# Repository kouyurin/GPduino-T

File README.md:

GPduino-T
=========
## 概要
GPduino-Tは、ESP32搭載のWiFiラジコン戦車制御ボードです。

以下のことができます。

* DCモータ4個を制御 (最大連続1.2A / 最大瞬間3.0A)
* LED 8個を制御
* サウンド出力
* 赤外線信号(38kHz変調)の送受信
* 電源 3.6V～7.2V (4.8～6V推奨)、電源電圧を監視
* WiFiによる通信　(APにもSTAにもなれる)

また、Waltersons製 1/24 バトルタンクシリーズ互換のIRバトルが可能なファームウェアを提供します。

## ファイル一覧

* hard/GPduino-T/
	* GPduino-T.sch/brd: 回路/基板設計データ(Eagle形式)
	* GPduino-T.pdf: 回路図(PDF)
	* GPduino-T_BOM.xlsx: BOMリスト(Excel形式)
	* GPduino-T.GBL/GBO/GBP/GBS/GML/GTL/GTO/GTP/GTS/TXT: ガーバデータ
* firm/GPduinoT/
	* GPduinoT.ino: ラジコン戦車のArduinoスケッチ
	* *.h, *.cpp: ラジコン戦車のための各種クラス宣言と実装 
* data/
	* cannon.bin: 砲撃音のサウンドデータ
* LICENSE: Apache Licence 2.0です。
	* ただし、回路/基板設計は、Creative Commons Attribution Share-Alike 3.0です。
* README.md これ

## Arduino開発環境のセットアップ
GPduino-T はESP32を搭載しており、Arduino IDEでファームウェアを開発できます。

ここでは、Windows10での開発環境のセットアップについて説明します。他のプラットフォームでも同様です。適宜読み替えてください。

* まず、ArduinoIDE をインストールしておきます。 (ここでは 1.8.2 を使用)
* 残念ながら、Arduino Core for the ESP32はArduino IDEのボードマネージャには対応しておらず、以下のように手作業でインストールする必要があります。
* まず、以下のリポジトリからクローンします。もしもGitが使えない場合、こちらからDownload ZIPして解凍してもかまいません。アップデートの時の手間だけの問題かと思います。
	* ソース: https://github.com/espressif/arduino-esp32.git
    * 保存先: C:/Users/ユーザ名/Documents/Arduino/hardware/espressif/esp32
* 次に、下記のバイナリを実行します。
	* C:/Users/ユーザ名/Documents/Arduino/hardware/espressif/esp32/tools/get.exe
* DOS窓が開いてインストールが実行されます。あとはDOS窓が閉じるまで待ちます。
* ノートン先生をはじめ一部のセキュリティソフトは、いくつかのバイナリをウィルスとして検出してしまうようです。(ノートン先生ではTrojan.Gen.8!cloudとして検出されます。)
* Arduino IDEの[ツール] > [マイコンボード]で[ESP32 Dev Module]を選択します。
* [ツール] > [Upload Speed]で[115200]を選択します。

## Arduinoスケッチ (Waltersonsバトルタンク互換)

Waltersons製 1/24 バトルタンクシリーズ互換の赤外線バトルが可能な以下のファームウェアを提供しています。
* firm/GPduinoT/
	* GPduinoT.ino: ラジコン戦車のArduinoスケッチ
	* *.h, *.cpp: ラジコン戦車のための各種クラス宣言と実装

Waltersonsのバトルタンクの制御基板と置き換える場合には、[こちら](http://d.hatena.ne.jp/licheng/20170421/p1)の結線表を参照してください。

## Arduinoスケッチ (ユーザー独自)
ユーザーが独自にファームウェアを作成する場合は、上記のスケッチを参考にしてください。

ラジコン戦車のための各種クラスを利用するためには、Wire.h と GPduinoR.h をインクルードします。
``` c
#include <Wire.h>
#include "GPduinoR.h"
```
すると、以下のクラスが使用できます。詳細はソースを参照してください。

* Battery: バッテリー電圧の取得
* DcMotor: DCモータの制御
* IR: 赤外線信号の送受信
* Led: LEDの制御
* Solenoid: ソレノイドの制御
* Sound: サウンドの出力
* UdpComm: WiFiによるUDP/IP通信

## Arduinoスケッチの書き込み
* GPduino-TをUSBケーブルでPCに接続します。
* 書き込み時もUSBからの給電は受けません。CN1から給電してください。
* Windows 7以降であればドライバが自動でインストールされ、COMポートとして認識されます。
	* 自動でデバイスが認識されない環境ではFTDIのデバイスドライバをインストールしてください。
* [ツール] > [シリアルポート]でESP32のポートを選択する。
* BOOTボタン(SW2)を押し下げた状態で、RESETボタン(SW1)を押して離します。これで書き込みモードになります。
* Uploadボタンで、ファームウェアを書き込みます。

## サウンドデータの書き込み
Arduinoスケッチとは別にサウンドデータもESP32のフラッシュメモリに書き込みます。

GPduinoT.ino は、フラッシュメモリの0x100000番地から61440バイトの領域に砲撃音のサウンドデータ (data/cannon.bin) が格納されているものとしています。

書き込みツール esptool.exe のあるディレクトリにパスを通しておきます。Windows10なら通常は下記ディレクトリになります。
```
C:\Users\ユーザ名\Documents\Arduino\hardware\espressif\esp32\tools
```
ESP32のBOOTボタン(SW2)を押し下げた状態で、RESETボタン(SW1)を押して離して書き込みモードにします。シリアルポートをPCに接続し、PCでCOMポート番号を確認します。ここではCOM3であったとします。そこで下記のコマンドを実行します。

```
esptool.exe -c esp32 -p COM3 -b 115200 write_flash 0x100000 cannon.bin
```

このサウンドデータは、下記のフォーマットのWAV形式ファイルから、先頭44バイトのヘッダを削除し、さらに符号なし16ビット値形式に変換するために各サンプル値に+0x8000したものです。
* サンプリング周波数 11.025kHz
* 符号つき16ビット量子化
* モノラル

## 既知の問題点

* ~~7.2V電源使用時に発熱が大きい。(3端子レギュレータをDCDCコンバータに置き換えるべき)~~ → rev.2で対応
* ~~サウンドのボリューム調整のためのトリマを追加すべき。~~ → rev.2で対応
* サウンド再生時にCPUがクラッシュする場合があるため、クラッシュ回避のごまかし処理を入れている。
* 無音時にアンプからプツプツ音が出る。
* ブリッジしやすいバターン要修正。 (SOP部品)
* D級アンプのランドパターンが短く、ハンダづけしづらい。

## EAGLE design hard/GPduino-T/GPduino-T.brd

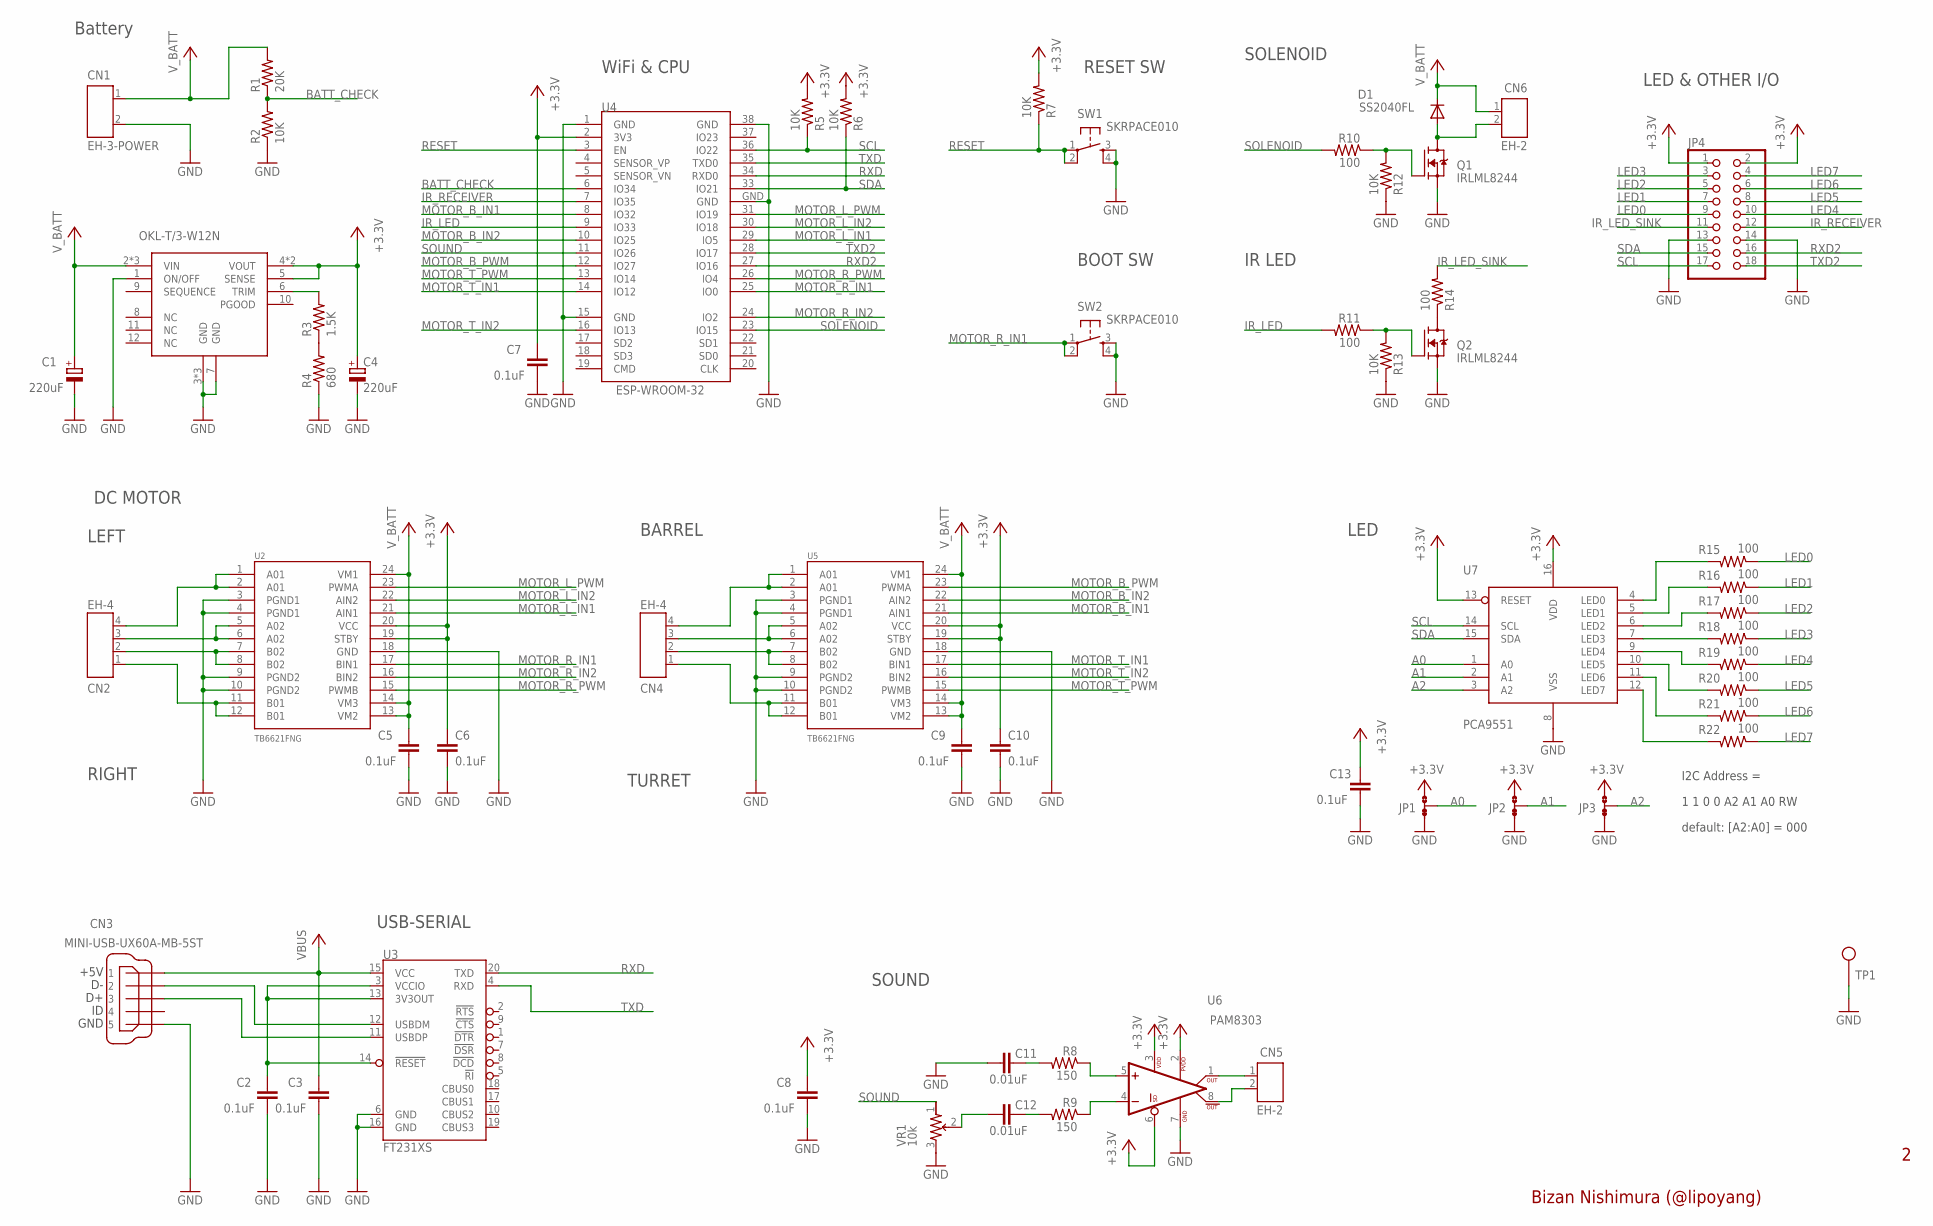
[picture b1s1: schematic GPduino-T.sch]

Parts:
C1, C4: 220uF; UD-6,3X7,7_NICHICON
C2, C3, C5, C6, C7, C8, C9, C10, C13: 0.1uF; C1608
C11, C12: 0.01uF; C1608
CN1: EH-3-POWER
CN2, CN4: EH-4
CN3: MINI-USB-UX60A-MB-5ST; UX60A-MB-5ST
CN5, CN6: EH-2
D1: SS2040FL; SOD123
JP1, JP2, JP3: JUMP-SHORTB; JUMP-SHORT
JP4: 2X09
Q1, Q2: IRLML8244; SOT23
R1: 20K; 0603-RES
R2, R5, R6, R7, R12, R13: 10K; 0603-RES
R3: 1.5K; 0603-RES
R4: 680; 0603-RES
R8, R9: 150; 0603-RES
R10, R11, R14, R15, R16, R17, R18, R19, R20, R21, R22: 100; 0603-RES
SW1, SW2: SKRPACE010
TP1: TEST_PIN
U1: OKL-T/3-W12N; OKL-T/X-WXXN
U2, U5: TB6621FNG; SSOP24
U3: FT231XS; SSOP20
U4: ESP-WROOM-32
U6: PAM8303; MSOP8
U7: PCA9551; TSSOP16
VR1: 10k; EVM3Y

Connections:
+3V3: C4.+, C6.1, C7.1, C8.1, C10.1, C13.1, JP1.1, JP2.1, JP3.1, JP4.1, JP4.2, R5.2, R6.2, R7.2, U1.4 (VOUT), U1.4@1 (VOUT), U1.5 (SENSE), U2.19 (STBY), U2.20 (VCC), U4.2 (3V3), U5.19 (STBY), U5.20 (VCC), U6.2 (PVDD), U6.3 (VDD), U6.6 (SD), U7.13 (RESET), U7.16 (VDD)
A0: JP1.2, U7.1 (A0)
A01: CN2.4, U2.1 (A01), U2.2 (A01)
A1: JP2.2, U7.2 (A1)
A02: CN2.3, U2.5 (A02), U2.6 (A02)
A2: JP3.2, U7.3 (A2)
A06: CN4.4, U5.1 (A01), U5.2 (A01)
A07: CN4.3, U5.5 (A02), U5.6 (A02)
BATT_CHECK: R1.1, R2.2, U4.6 (IO34)
GND: C1.-, C2.2, C3.2, C4.-, C5.2, C6.2, C7.2, C8.2, C9.2, C10.2, C11.2, C13.2, CN1.2, CN3.5, JP1.3, JP2.3, JP3.3, JP4.13, JP4.14, Q1.2 (S), Q2.2 (S), R2.1, R4.1, R12.1, R13.1, SW1.3, SW1.4, SW2.3, SW2.4, TP1.1, U1.1 (ON/OFF), U1.3 (GND), U1.3@2 (GND), U1.3@3 (GND), U1.7 (GND), U2.3 (PGND1), U2.4 (PGND1), U2.9 (PGND2), U2.10 (PGND2), U2.18 (GND), U3.6 (GND), U3.16 (GND), U4.1 (GND), U4.15 (GND), U4.38 (GND), U4.GND, U5.3 (PGND1), U5.4 (PGND1), U5.9 (PGND2), U5.10 (PGND2), U5.18 (GND), U6.7 (GND), U7.8 (VSS), VR1.3 (A)
IR_LED: R11.2, U4.9 (IO33)
IR_LED_SINK: JP4.11, R14.2
IR_RECEIVER: JP4.12, U4.7 (IO35)
LED0: JP4.9, R15.1
LED1: JP4.7, R16.1
LED2: JP4.5, R17.1
LED3: JP4.3, R18.1
LED4: JP4.10, R19.1
LED5: JP4.8, R20.1
LED6: JP4.6, R21.1
LED7: JP4.4, R22.1
MOTOR_B_IN1: U4.8 (IO32), U5.21 (AIN1)
MOTOR_B_IN2: U4.10 (IO25), U5.22 (AIN2)
MOTOR_B_PWM: U4.12 (IO27), U5.23 (PWMA)
MOTOR_L_IN1: U2.21 (AIN1), U4.29 (IO5)
MOTOR_L_IN2: U2.22 (AIN2), U4.30 (IO18)
MOTOR_L_PWM: U2.23 (PWMA), U4.31 (IO19)
MOTOR_R_IN1: SW2.1, SW2.2, U2.17 (BIN1), U4.25 (IO0)
MOTOR_R_IN2: U2.16 (BIN2), U4.24 (IO2)
MOTOR_R_PWM: U2.15 (PWMB), U4.26 (IO4)
MOTOR_T_IN1: U4.14 (IO12), U5.17 (BIN1)
MOTOR_T_IN2: U4.16 (IO13), U5.16 (BIN2)
MOTOR_T_PWM: U4.13 (IO14), U5.15 (PWMB)
unnamed: CN6.2, D1.A, Q1.3 (D)
unnamed: CN4.1, U5.11 (B01), U5.12 (B01)
unnamed: Q1.1 (G), R10.1, R12.2
unnamed: CN4.2, U5.7 (B02), U5.8 (B02)
unnamed: CN2.1, U2.11 (B01), U2.12 (B01)
unnamed: CN2.2, U2.7 (B02), U2.8 (B02)
unnamed: Q2.1 (G), R11.1, R13.2
unnamed: Q2.3 (D), R14.1
unnamed: R22.2, U7.12 (LED7)
unnamed: CN3.2, U3.12 (USBDM)
unnamed: CN3.3, U3.11 (USBDP)
unnamed: C2.1, U3.3 (VCCIO), U3.13 (3V3OUT), U3.14 (!RESET)
unnamed: R21.2, U7.11 (LED6)
unnamed: R20.2, U7.10 (LED5)
unnamed: R19.2, U7.9 (LED4)
unnamed: R18.2, U7.7 (LED3)
unnamed: R17.2, U7.6 (LED2)
unnamed: R16.2, U7.5 (LED1)
unnamed: R15.2, U7.4 (LED0)
unnamed: R8.1, U6.5 (IN+)
unnamed: R9.1, U6.4 (IN-)
unnamed: CN5.1, U6.1 (OUT+)
unnamed: C11.1, R8.2
unnamed: C12.1, R9.2
unnamed: CN5.2, U6.8 (OUT-)
unnamed: C12.2, VR1.2 (S)
unnamed: R3.1, R4.2
unnamed: R3.2, U1.6 (TRIM)
RESET: R7.1, SW1.1, SW1.2, U4.3 (EN)
RXD: U3.20 (TXD), U4.34 (RXD0)
RXD2: JP4.16, U4.27 (IO16)
SCL: JP4.17, R5.1, U4.36 (IO22), U7.14 (SCL)
SDA: JP4.15, R6.1, U4.33 (IO21), U7.15 (SDA)
SOLENOID: R10.2, U4.23 (IO15)
SOUND: U4.11 (IO26), VR1.1 (E)
TXD: U3.4 (RXD), U4.35 (TXD0)
TXD2: JP4.18, U4.28 (IO17)
VBUS: C3.1, CN3.1, U3.15 (VCC)
V_BATT: C1.+, C5.1, C9.1, CN1.1, CN6.1, D1.C, R1.2, U1.2 (VIN), U1.2@2 (VIN), U1.2@3 (VIN), U2.13 (VM2), U2.14 (VM3), U2.24 (VM1), U5.13 (VM2), U5.14 (VM3), U5.24 (VM1)

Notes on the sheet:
Battery
LEFT
Bizan Nishimura (@lipoyang)
RIGHT
1 1 0 0 A2 A1 A0 RW
I2C Address =
default: [A2:A0] = 000
USB-SERIAL
DC MOTOR
WiFi & CPU
RESET SW
BOOT SW
TURRET
BARREL
SOLENOID
IR LED
LED & OTHER I/O
LED
SOUND

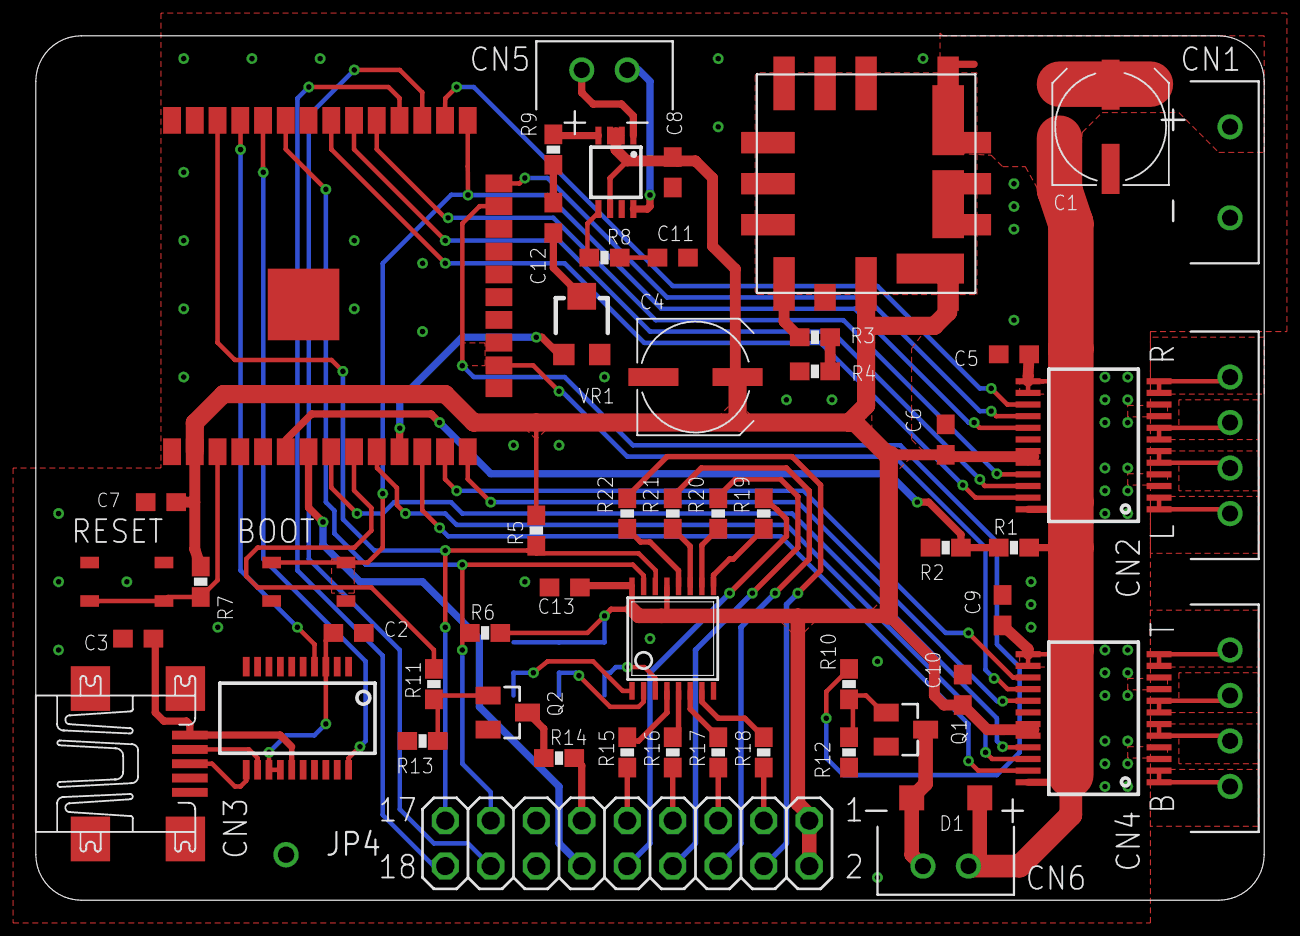
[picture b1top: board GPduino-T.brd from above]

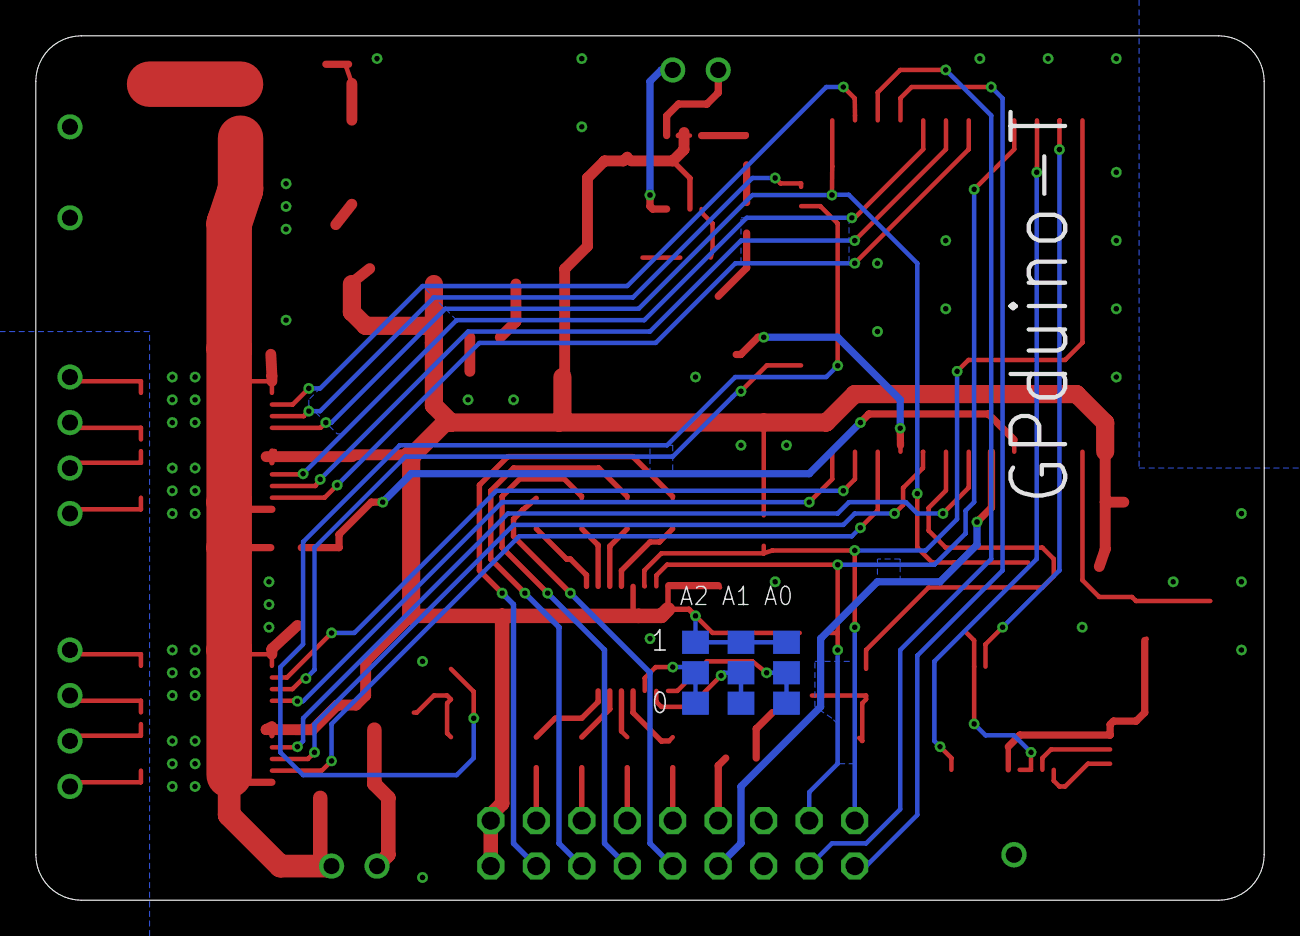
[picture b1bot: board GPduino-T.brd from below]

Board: 2 copper layers, 68.6 x 48.3 mm, 59 parts (3 on the bottom side), 72 nets.

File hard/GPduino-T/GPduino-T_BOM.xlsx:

Gpduino-T BOM
No | Reference | Part Number | Vender | Description | DNP | Qty | Unit Price | Price | Lot Size | Supplier | Supplier Code
1 | C1,4 | 220u10V | NICHICON | チップアルミ電解コンデンサ ニチコンWTデンカイ |  | 2 | 10 | 20 | 1 | 秋月アキヅキ | P-10419
2 | C2,3,5-10,13 | 0.1u(1608) | (generic) | 1608型ガタ |  | 9 | 0.32500000000000001 | 2.9250000000000003 | 4000 | 秋月アキヅキ | P-01299
3 | C11,12 | 10nF(1608) | (generic) | 1608型ガタ |  | 2 | 1 | 2 | 100 | 秋月アキヅキ | P-04660
4 | CN1 | B3B-EH | JST | EH 3極 I型ポストキョクガタ | DNP | 0 | 21 | 0 | 1 | 共立キョウリツ | -
5 | CN2 | MUSB-5B-NE-S175 | Useconn Electronics | USBコネクタ Mini B メス |  | 1 | 50 | 50 | 2 | 秋月アキヅキ | C-05843
6 | CN3,4 | B4B-EH | JST | EH 4極 I型ポストキョクガタ | DNP | 0 | 21 | 0 | 1 | 共立キョウリツ | -
7 | CN5,6 | B2B-EH | JST | EH 2極 I型ポストキョクガタ | DNP | 0 | 16 | 0 | 1 | 共立キョウリツ | -
8 | CN7 | - | (generic) | 2.54mmピッチ 9ピン×2列 L字ピンヘッダレツジ | DNP | 0 | 77 | 0 | 4 | 共立キョウリツ | -
9 | D1 | SS2040FL | PANJIT | ショットキーバリアダイオード 40V2A |  | 1 | 15 | 15 | 20 | 秋月アキヅキ | I-02073
10 | Q1,2 | IRLML8244 | International Rectifier | Nch MOSFET (SOT23パッケージ) |  | 1 | 13 | 13 | 10 | 秋月アキヅキ | I-06051
11 | R1 | 20k(1608) | (generic) | 1608型 |  | 1 | 0.2 | 0.2 | 2500 | 秋月アキヅキ | R-06203
12 | R2,5-7,12,13 | 10k(1608) | (generic) | 1608型 |  | 6 | 0.2 | 1.2000000000000002 | 2500 | 秋月アキヅキ | R-06103
13 | R3 | 1.5k(1608) | (generic) | 1608型、±0.1% |  | 1 | 57.6 | 57.6 | 5 | RS | 566-872
14 | R4 | 680(1608) | (generic) | 1608型、±0.1% |  | 1 | 57.6 | 57.6 | 5 | RS | 566-361
15 | R8,9 | 150(1608) | (generic) | 1608型 |  | 2 | 0.2 | 0.4 | 2500 | 秋月アキヅキ | R-06151
16 | R10,11,14-19 | 100(1608) | (generic) | 1608型 |  | 8 | 0.2 | 1.6 | 2500 | 秋月アキヅキ | R-06101
17 | R20-22 | 100(1608) | (generic) | 1608型 | DNP | 0 | 0.2 | 0 | 2500 | 秋月アキヅキ | R-06101
18 | SW1,2 | SKRPACE010 | ALPS | 表面実装タクトスイッチヒョウメンジッソウ |  | 2 | 20 | 40 | 5 | 秋月アキヅキ | P-06185
19 | U1 | OKL-T/3-W12N | Murata | DCDCコンバータ |  | 1 | 400 | 400 | 1 | 秋月アキヅキ | M-06206
20 | U2,5 | TB6621FNG | Toshiba | Dual DCモータドライバ |  | 2 | 306 | 612 | 1 | RS | 770-3797
21 | U3 | FT231XS | FTDI | USBシリアル変換ヘンカン |  | 1 | 210 | 210 | 1 | 秋月アキヅキ | I-06713
22 | U4 | ESP-WROOM-32 | Espressif Systems | ESP32 WiFiマイコン |  | 1 | 700 | 700 | 1 | 秋月アキヅキ | M-11647
23 | U6 | PAM8303 CBSC | DiodesZetex | オーディオD級アンプキュウ |  | 1 | 32.6 | 32.6 | 10 | RS | 790-2966
24 | U7 | PCA9551 PW | NXP | 8チャンネルLEDドライバ |  | 1 | 111 | 111 | 5 | RS | 510-730
25 | VR1 | EVM3YSX50B14 | Panasonic | 半固定抵抗器 10kΩ, 0.15W |  | 1 | 54.2 | 54.2 | 5 | RS | 731-2883
26 | - | - | Elecrow | 基板キバン |  | 1 | 275.10000000000002 | 275.10000000000002 | 10 | Elecrow | -
 |  |  |  |  |  |  | Total | 2656.4249999999997

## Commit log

2017-07-29 回路設計データを追加
2017-07-29 READMEを追加
2017-07-29 ファーウェアの追加
2017-08-02 READMEを修正
2017-08-02 砲撃サウンドデータの追加
2017-08-02 READMEの修正
2017-10-24 rev.2基板

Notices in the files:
parts and their libraries:
lipoyang_frame: Released under the Creative Commons
Attribution Share-Alike 3.0 License
http://creativecommons.org/licenses/by-sa/3.0
